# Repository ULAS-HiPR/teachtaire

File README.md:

# Teachtaire

Teachtaire is the telemetry and navigation node in [Ogma](https://sean-osullivan.com/projects/ogma/), the University of Limerick Aeronautics Society's modular avionics stack for high-powered rocketry.

## Role

- Relays stack telemetry over an SX1272 LoRa radio.
- Reads position and timing from a u-blox MAX-M10S GNSS receiver.
- Exchanges telemetry and status over the 500 kbit/s CAN bus.
- Runs on an STM32F072.

## Repository

- `hardware/` - KiCad design and manufacturing outputs.
- `firmware/` - embedded firmware, radio/GNSS probes, and tests.

## Status

Rev 1 firmware and hardware bring-up continue on [`ogma/flight-hardening`](https://github.com/ULAS-HiPR/teachtaire/tree/ogma/flight-hardening). Release-candidate firmware builds and software tests pass, but hardware-in-the-loop validation is still underway. Teachtaire is not yet flight-proven.

## Manufacturing support

Rev 1 PCB fabrication was sponsored through [EasyEDA Education](https://easyeda.com/education) and manufactured by [JLCPCB](https://jlcpcb.com/). The board was designed in KiCad and imported into EasyEDA Pro for the sponsorship and manufacturing workflow.

## More information

See the [Ogma project write-up](https://sean-osullivan.com/projects/ogma/) for the complete stack, bring-up work, and current status.

> [!WARNING]
> This project is archived, and is no longer actively supported.
> Contact us for more details.

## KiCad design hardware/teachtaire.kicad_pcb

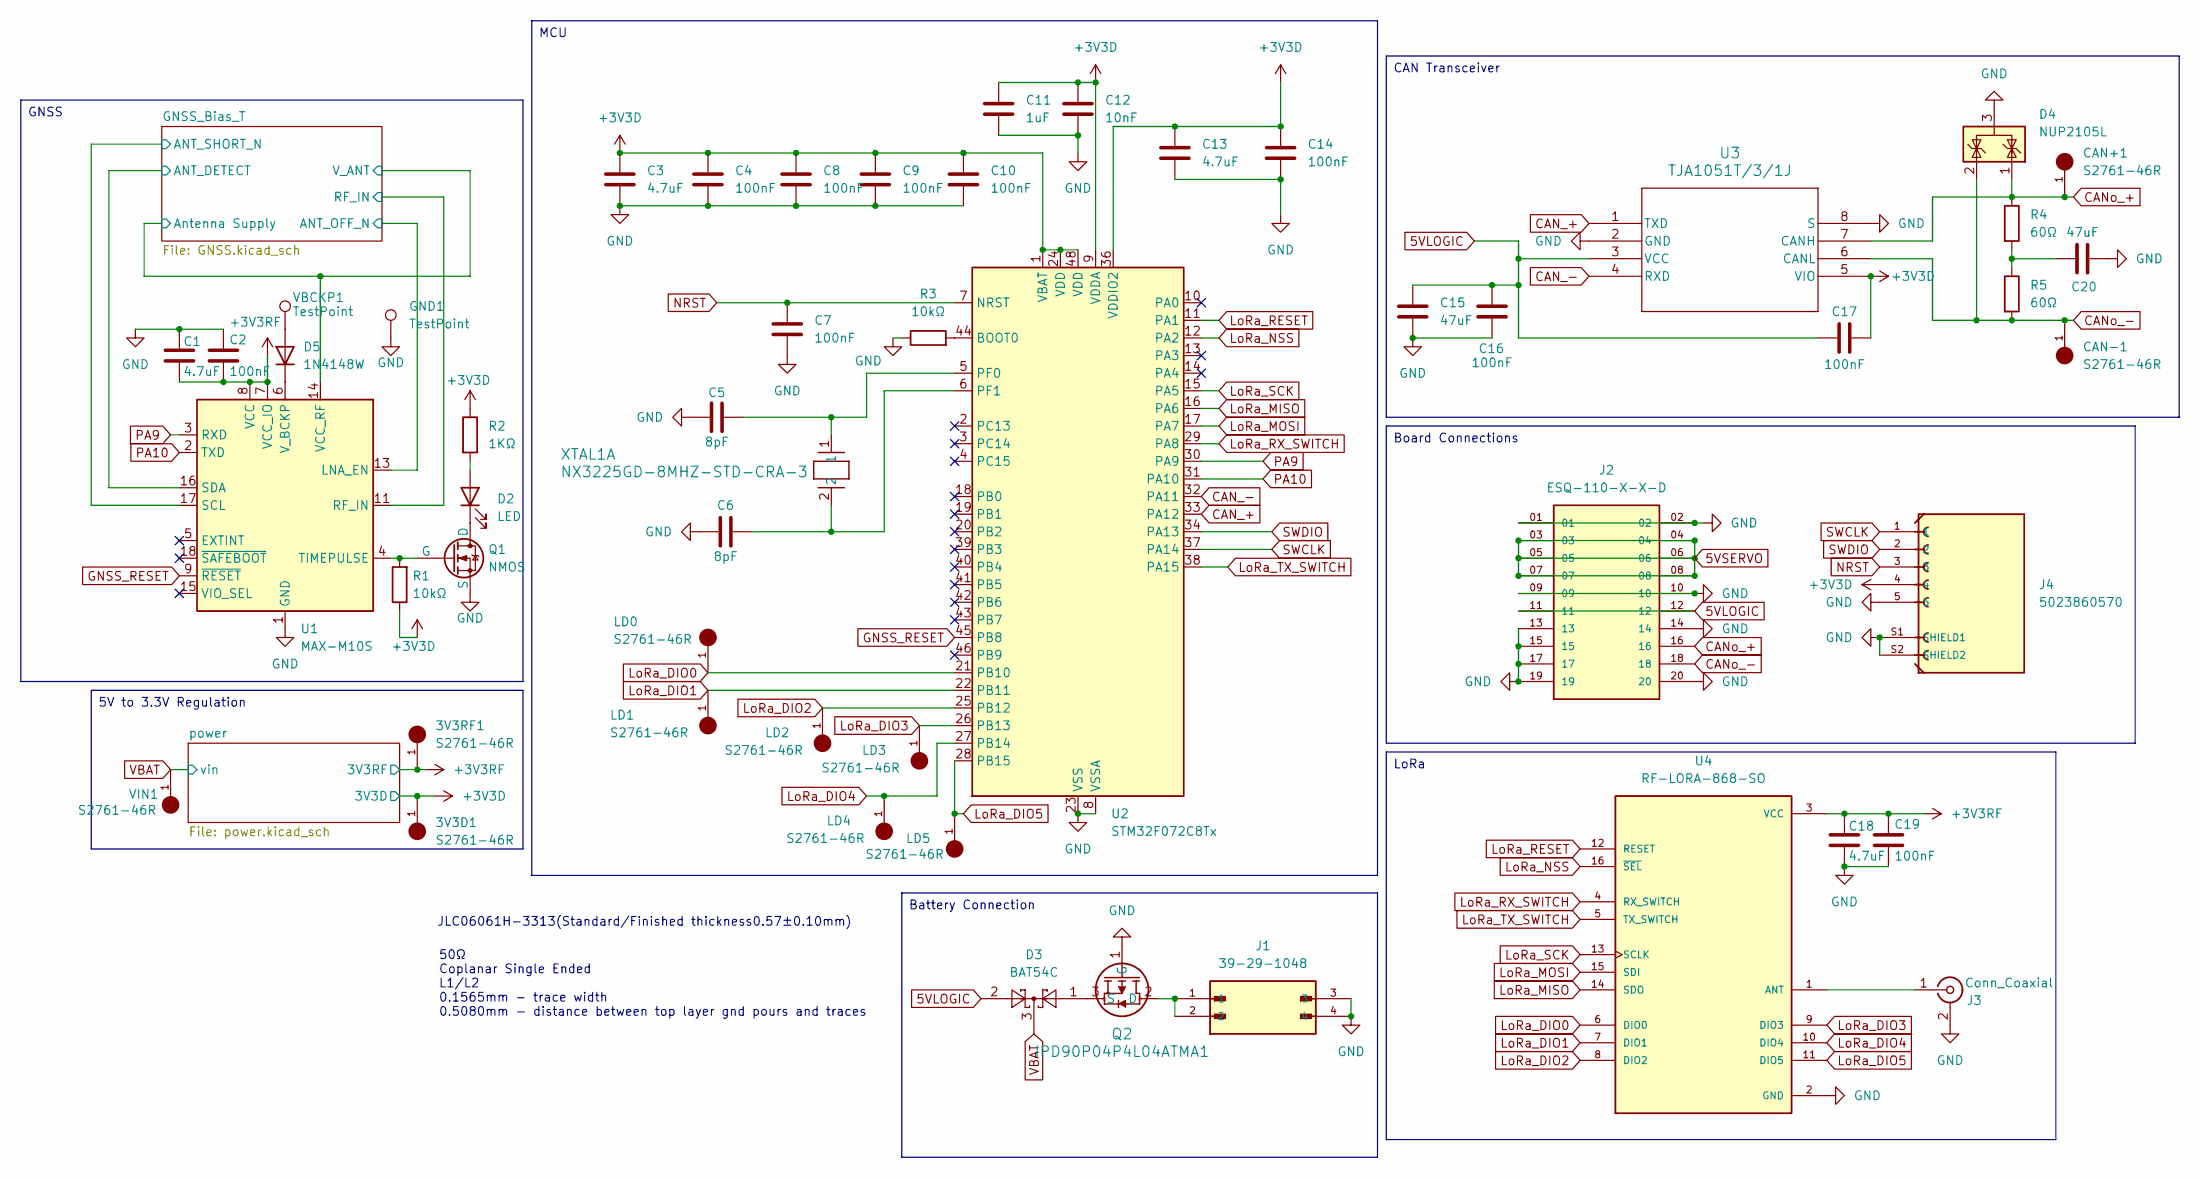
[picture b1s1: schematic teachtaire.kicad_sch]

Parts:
3V3D1, 3V3RF1: S2761-46R; HARWIN_S2761-46R; PARTREV 1
C1, C3, C13, C18: 4.7uF; C_0402_1005Metric
C2, C4, C7, C8, C9, C10, C14, C16, C17, C19: 100nF; C_0402_1005Metric
C5, C6: 8pF; C_0402_1005Metric
C11: 1uF; C_0402_1005Metric
C12: 10nF; C_0603_1608Metric
C15, C20: 47uF; C_0603_1608Metric
CAN+1: S2761-46R; HARWIN_S2761-46R; PARTREV 1
CAN-1: S2761-46R; HARWIN_S2761-46R; PARTREV 1
D2: LED; LED_0402_1005Metric
D3: BAT54C; SOT-23
D4: NUP2105L; SOT-23
D5: 1N4148W; D_SOD-123
GND1: TestPoint; TestPoint_Pad_D2.0mm
J1: 39-29-1048; MOLEX_39-29-1048
J2: ESQ-110-X-X-D; SAMTEC_ESQ-110-14-G-D; PARTREV NA
J3: Conn_Coaxial; SMA_BAT_Wireless_BWSMA-KWE-Z001
J4: 5023860570; MOLEX_5023860570; PARTREV F
LD0, LD1, LD2, LD3, LD4, LD5: S2761-46R; HARWIN_S2761-46R; PARTREV 1
Q1: NMOS; SOT-23
Q2: IPD90P04P4L04ATMA1; PG-TO252-3-313_INF-L
R1, R3: 10kΩ; R_0402_1005Metric
R2: 1KΩ; R_0402_1005Metric
R4, R5: 60Ω; R_0402_1005Metric
U1: MAX-M10S; ublox_MAX
U2: STM32F072C8Tx; LQFP-48_7x7mm_P0.5mm
U3: TJA1051T/3/1J; SO8_SOT96-1_NXP
U4: RF-LORA-868-SO; XCVR_RF-LORA-868-SO
VBCKP1: TestPoint; TestPoint_Pad_D2.0mm
VIN1: S2761-46R; HARWIN_S2761-46R; PARTREV 1
XTAL1: NX3225GD-8MHZ-STD-CRA-3; XTAL_NX3225GD-8MHZ-STD-CRA-3_NDK

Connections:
5VLOGIC: C15.1, C16.1, C17.1, D3.2, J2.11, J2.12, U3.3 (VCC)
5VSERVO: J2.03, J2.04, J2.05, J2.06, J2.07, J2.08
+3V3D: 3V3D1.1, C3.1, C4.1, C8.1, C9.1, C10.1, C11.1, C12.1, C13.1, C14.1, C17.2, J4.4, R1.1, R2.1, U2.1 (VBAT), U2.9 (VDDA), U2.24 (VDD), U2.36 (VDDIO2), U2.48 (VDD), U3.5 (VIO); also elsewhere on the board
+3V3RF: 3V3RF1.1, C1.2, C2.2, C18.1, C19.1, U1.7 (VCC_IO), U1.8 (VCC), U4.3 (VCC); also elsewhere on the board
/GNSS_Bias_T/ANT_DETECT: U1.16 (SDA); also elsewhere on the board
/GNSS_Bias_T/ANT_OFF_N: U1.13 (LNA_EN); also elsewhere on the board
/GNSS_Bias_T/ANT_SHORT_N: U1.17 (SCL); also elsewhere on the board
/GNSS_Bias_T/Antenna Supply: U1.14 (VCC_RF); also elsewhere on the board
/GNSS_Bias_T/RF_IN: U1.11 (RF_IN); also elsewhere on the board
CAN_+: U2.33 (PA12), U3.1 (TXD)
CAN_-: U2.32 (PA11), U3.4 (RXD)
CANo_+: CAN+1.1, D4.1 (K), J2.16, R4.1, U3.7 (CANH); also elsewhere on the board
CANo_-: CAN-1.1, D4.2 (K), J2.18, R5.2, U3.6 (CANL); also elsewhere on the board
GND: C1.1, C2.1, C3.2, C4.2, C5.1, C6.1, C7.2, C8.2, C9.2, C10.2, C11.2, C12.2, C13.2, C14.2, C15.2, C16.2, C18.2, C19.2, C20.2, D4.3 (A), GND1.1, J1.3, J1.4, J2.01, J2.02, J2.09, J2.10, J2.13, J2.14, J2.15, J2.17, J2.19, J2.20, J3.2 (Ext), J4.5, J4.S1 (SHIELD1), J4.S2 (SHIELD2), Q1.3 (S), Q2.1 (G), R3.1, U1.1 (GND), U1.10 (GND), U1.12 (GND), U2.8 (VSSA), U2.23 (VSS), U2.35 (VSS), U2.47 (VSS), U3.2 (GND), U3.8 (S), U4.2 (GND); also elsewhere on the board
GNSS_RESET: U1.9 (~RESET), U2.45 (PB8)
LoRa_DIO0: LD0.1, U2.21 (PB10), U4.6 (DIO0)
LoRa_DIO1: LD1.1, U2.22 (PB11), U4.7 (DIO1)
LoRa_DIO2: LD2.1, U2.25 (PB12), U4.8 (DIO2)
LoRa_DIO3: LD3.1, U2.26 (PB13), U4.9 (DIO3)
LoRa_DIO4: LD4.1, U2.27 (PB14), U4.10 (DIO4)
LoRa_DIO5: LD5.1, U2.28 (PB15), U4.11 (DIO5)
LoRa_MISO: U2.16 (PA6), U4.14 (SDO)
LoRa_MOSI: U2.17 (PA7), U4.15 (SDI)
LoRa_NSS: U2.12 (PA2), U4.16 (~SEL)
LoRa_RESET: U2.11 (PA1), U4.12 (RESET)
LoRa_RX_SWITCH: U2.29 (PA8), U4.4 (RX_SWITCH)
LoRa_SCK: U2.15 (PA5), U4.13 (SCLK)
LoRa_TX_SWITCH: U2.38 (PA15), U4.5 (TX_SWITCH)
NRST: C7.1, J4.3, U2.7 (NRST)
unnamed: C20.1, R4.2, R5.1
unnamed: D2.2 (A), R2.2
unnamed: D2.1 (K), Q1.1 (D)
unnamed 33: D5.2 (A), VBCKP1.1; also elsewhere on the board
unnamed: D5.1 (K), U1.6 (V_BCKP)
unnamed: J3.1 (In), U4.1 (ANT)
unnamed: Q1.2 (G), R1.2, U1.4 (TIMEPULSE)
unnamed: J1.1, J1.2, Q2.2 (D)
unnamed: D3.1, Q2.3 (S)
unnamed: R3.2, U2.44 (BOOT0)
unnamed: C5.2, U2.5 (PF0), XTAL1.1
unnamed: C6.2, U2.6 (PF1), XTAL1.2
PA9: U1.3 (RXD), U2.30 (PA9)
PA10: U1.2 (TXD), U2.31 (PA10)
SWCLK: J4.1, U2.37 (PA14)
SWDIO: J4.2, U2.34 (PA13)
VBAT: D3.3, VIN1.1; also elsewhere on the board

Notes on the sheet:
50Ω Coplanar Single Ended L1/L2 0.1565mm - trace width 0.5080mm - distance between top layer gnd pours and traces
JLC06061H-3313(Standard/Finished thickness0.57±0.10mm)
Board Connections
Battery Connection
LoRa
CAN Transceiver
GNSS
MCU
5V to 3.3V Regulation

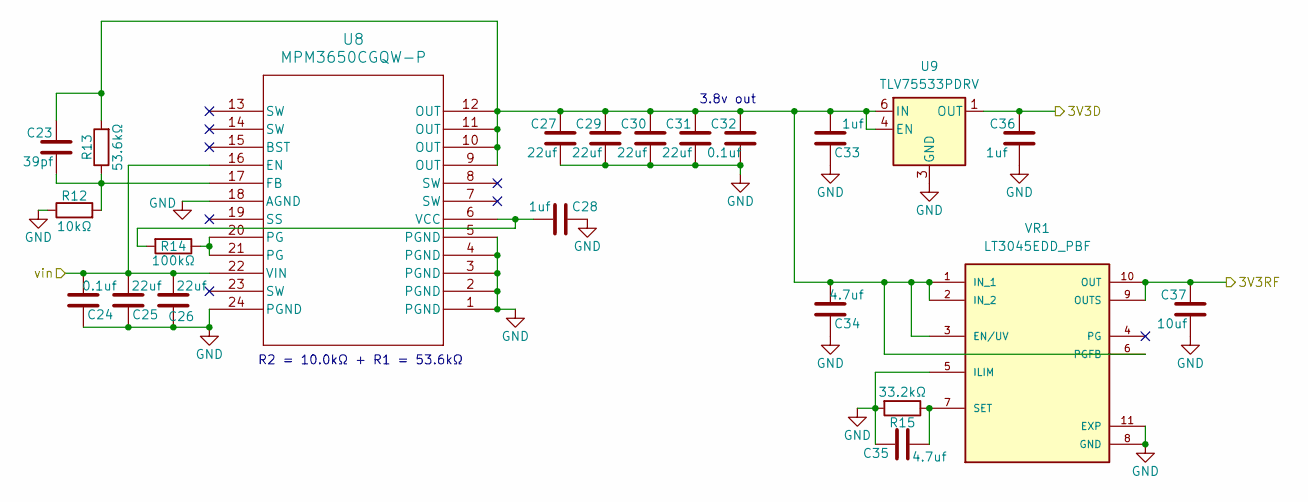
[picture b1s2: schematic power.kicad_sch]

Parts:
C23: 39pf; C_0402_1005Metric
C24, C32: 0.1uf; C_0402_1005Metric
C25, C26, C27, C29, C30, C31: 22uf; C_0603_1608Metric
C28, C33, C36: 1uf; C_0402_1005Metric
C34, C35: 4.7uf; C_0402_1005Metric
C37: 10uf; C_0603_1608Metric
R12: 10kΩ; R_0402_1005Metric
R13: 53.6kΩ; R_0402_1005Metric
R14: 100kΩ; R_0402_1005Metric
R15: 33.2kΩ; R_0402_1005Metric
U8: MPM3650CGQW-P; QFN-24_MPM3650_MNP
U9: TLV75533PDRV; WSON-6-1EP_2x2mm_P0.65mm_EP1x1.6mm
VR1: LT3045EDD_PBF; SON50P300X300X80-11N; PARTREV C

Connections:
+3V3D: C36.1, U9.1 (OUT); also elsewhere on the board
+3V3RF: C37.1, VR1.9 (OUTS), VR1.10 (OUT); also elsewhere on the board
GND: C24.1, C25.1, C26.1, C27.2, C28.1, C29.2, C30.2, C31.2, C32.2, C33.1, C34.1, C35.1, C36.2, C37.2, R12.1, R15.2, U8.1 (PGND), U8.2 (PGND), U8.3 (PGND), U8.4 (PGND), U8.5 (PGND), U8.18 (AGND), U8.24 (PGND), U9.3 (GND), U9.7 (GND), VR1.5 (ILIM), VR1.8 (GND), VR1.11 (EXP); also elsewhere on the board
unnamed: R14.1, U8.20 (PG), U8.21 (PG)
unnamed: C23.2, R12.2, R13.1, U8.17 (FB)
unnamed: C28.2, R14.2, U8.6 (VCC)
unnamed: C23.1, C27.1, C29.1, C30.1, C31.1, C32.1, C33.2, C34.2, R13.2, U8.9 (OUT), U8.10 (OUT), U8.11 (OUT), U8.12 (OUT), U9.4 (EN), U9.6 (IN), VR1.1 (IN_1), VR1.2 (IN_2), VR1.3 (EN/UV), VR1.6 (PGFB)
unnamed: C35.2, R15.1, VR1.7 (SET)
VBAT: C24.2, C25.2, C26.2, U8.16 (EN), U8.22 (VIN); also elsewhere on the board

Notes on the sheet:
3.8v out
R2 = 10.0kΩ + R1 = 53.6kΩ

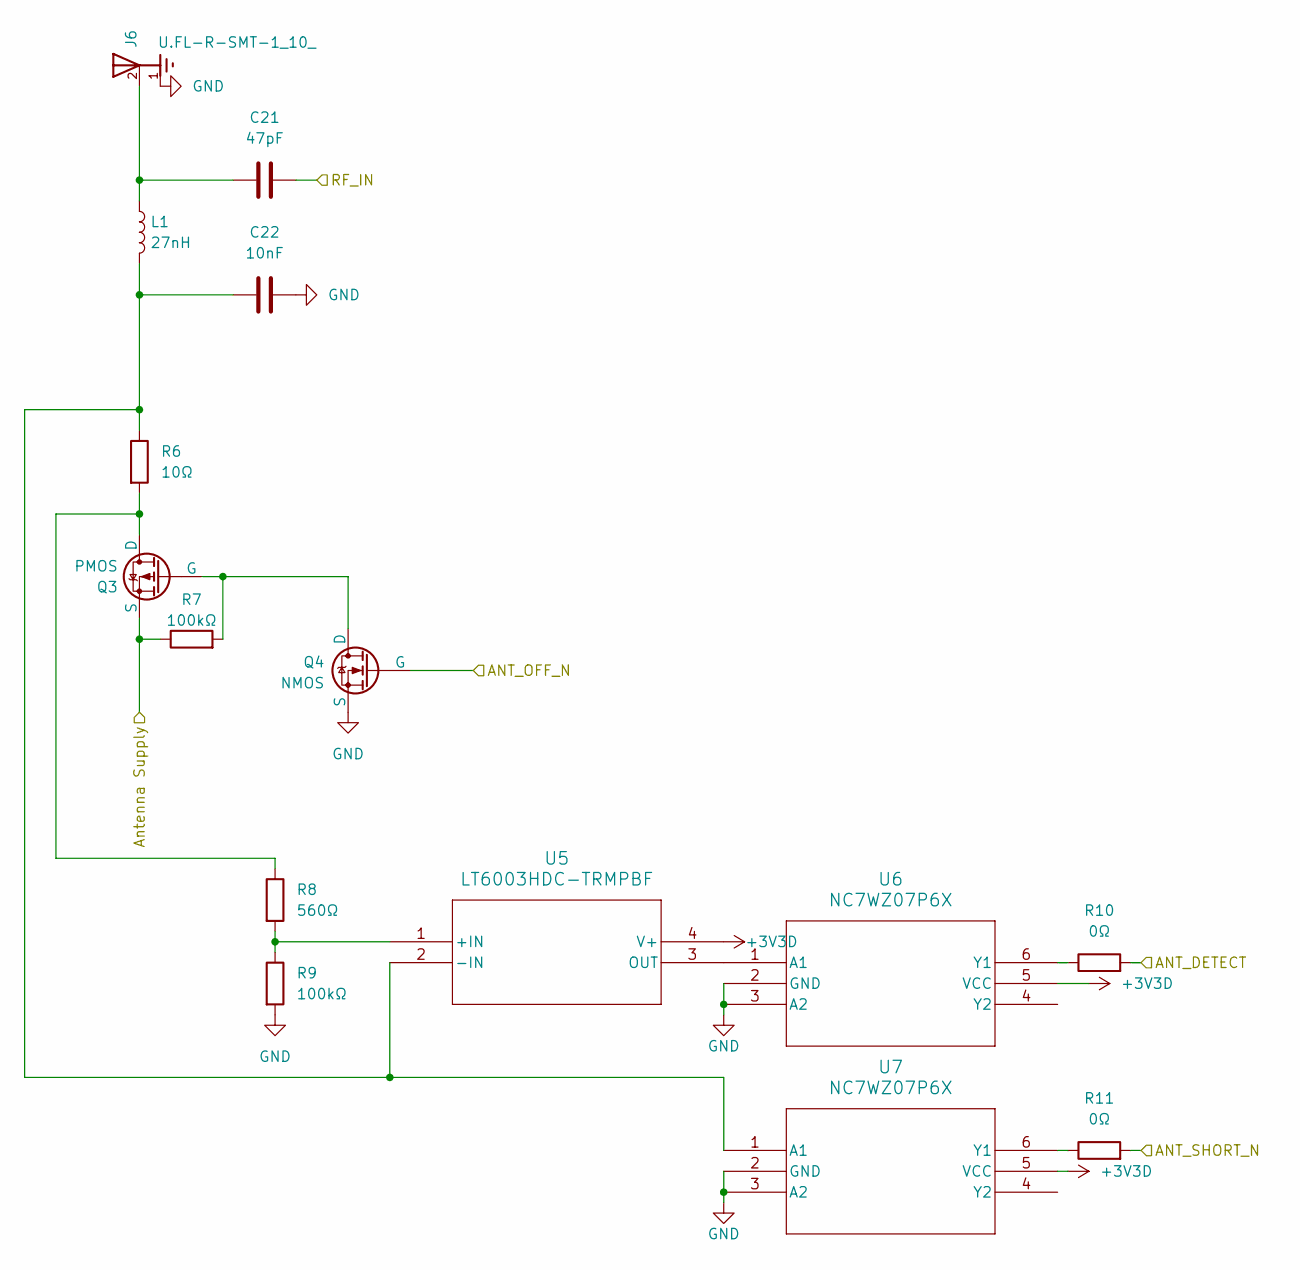
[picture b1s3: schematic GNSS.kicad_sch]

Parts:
C21: 47pF; C_0402_1005Metric
C22: 10nF; C_0603_1608Metric
J6: U.FL-R-SMT-1_10_; HRS_U.FL-R-SMT-1_10_
L1: 27nH; L_0402_1005Metric
Q3: PMOS; SOT-23
Q4: NMOS; SOT-23
R6: 10Ω; R_0402_1005Metric
R7, R9: 100kΩ; R_0402_1005Metric
R8: 560Ω; R_0402_1005Metric
R10, R11: 0Ω; R_0402_1005Metric
U5: LT6003HDC-TRMPBF; DC_4_ADI
U6, U7: NC7WZ07P6X; SC-88&slash_SC70-6&slash_SOT-363_419B-02_ONS

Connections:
+3V3D: U5.4 (V+), U6.5 (VCC), U7.5 (VCC); also elsewhere on the board
/GNSS_Bias_T/ANT_DETECT: R10.2; also elsewhere on the board
/GNSS_Bias_T/ANT_OFF_N: Q4.2 (G); also elsewhere on the board
/GNSS_Bias_T/ANT_SHORT_N: R11.2; also elsewhere on the board
/GNSS_Bias_T/Antenna Supply: Q3.3 (S), R7.1; also elsewhere on the board
/GNSS_Bias_T/RF_IN: C21.2; also elsewhere on the board
GND: C22.2, J6.1, J6.3, Q4.3 (S), R9.2, U6.2 (GND), U6.3 (A2), U7.2 (GND), U7.3 (A2); also elsewhere on the board
unnamed: C21.1, J6.2, L1.1
unnamed: Q3.1 (D), R6.2, R8.1
unnamed: Q3.2 (G), Q4.1 (D), R7.2
unnamed: R8.2, R9.1, U5.1 (+IN)
unnamed: C22.1, L1.2, R6.1, U5.2 (-IN), U7.1 (A1)
unnamed: U5.3 (OUT), U6.1 (A1)
unnamed: R10.1, U6.6 (Y1)
unnamed: R11.1, U7.6 (Y1)

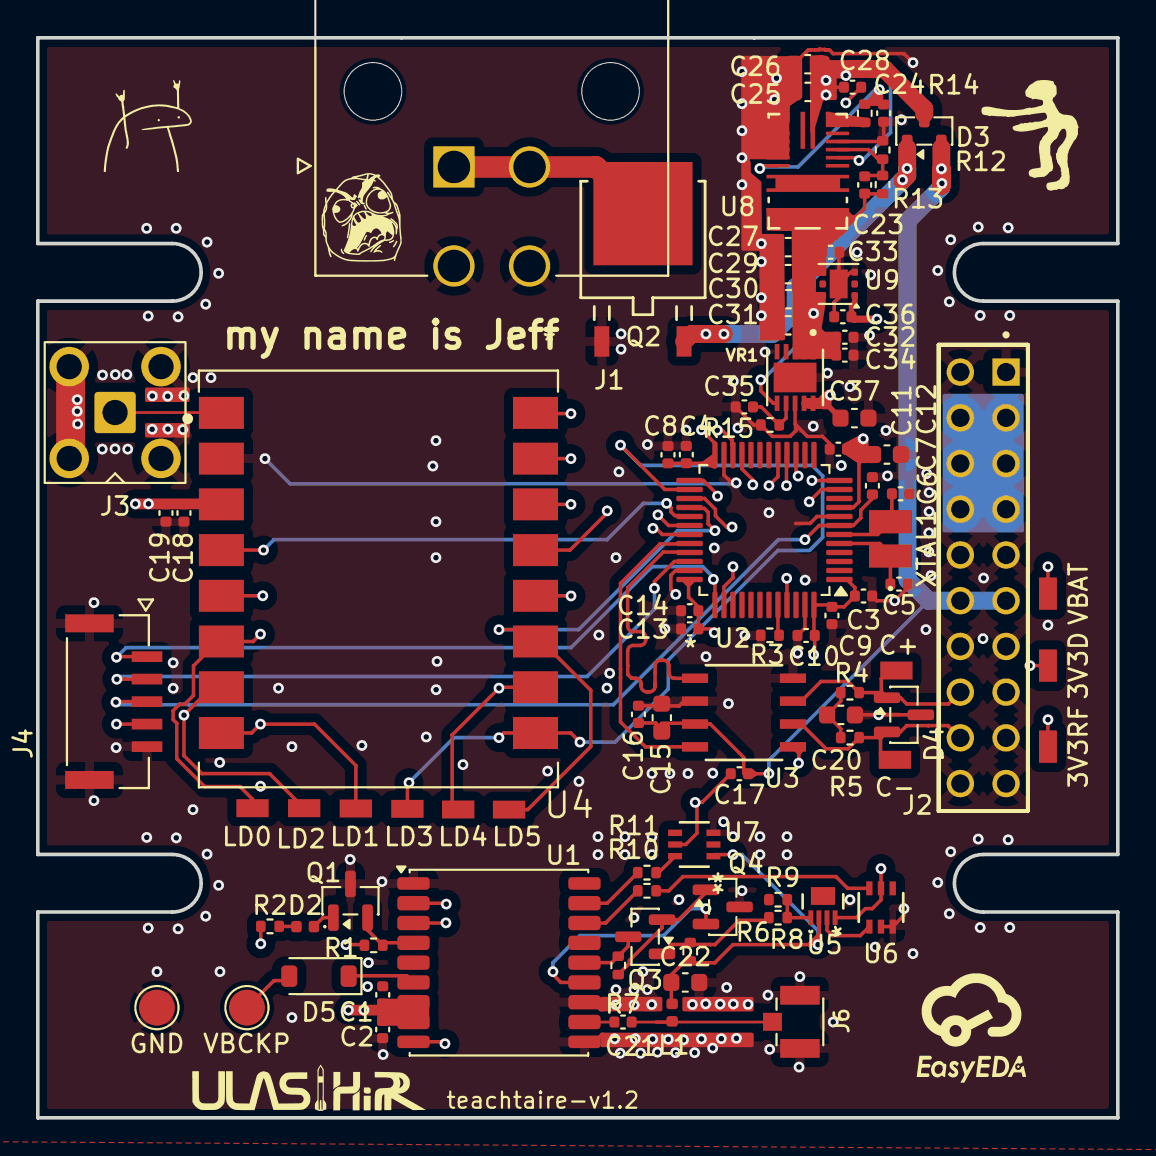
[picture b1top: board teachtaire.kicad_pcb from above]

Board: 6 copper layers, 60.0 x 60.0 mm, 90 parts (0 on the bottom side), 59 nets.

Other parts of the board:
3V3D, 3V3RF: S2761-46R; HARWIN_S2761-46R
C+: S2761-46R; HARWIN_S2761-46R
C-: S2761-46R; HARWIN_S2761-46R
GND: TestPoint; TestPoint_Pad_D2.0mm
VBAT: S2761-46R; HARWIN_S2761-46R
VBCKP: TestPoint; TestPoint_Pad_D2.0mm

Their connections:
+3V3D: 3V3D.1; also elsewhere on the board
+3V3RF: 3V3RF.1; also elsewhere on the board
CANo_+: C+.1; also elsewhere on the board
CANo_-: C-.1; also elsewhere on the board
GND: GND.1; also elsewhere on the board
unnamed 33: VBCKP.1; also elsewhere on the board
VBAT: VBAT.1; also elsewhere on the board

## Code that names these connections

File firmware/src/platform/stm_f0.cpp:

#if F0
#include "stm_f0.h"


CAN_HandleTypeDef hcan;
SPI_HandleTypeDef hspi1;
UART_HandleTypeDef huart1;

void HAL_MspInit(void)
{

  /* USER CODE BEGIN MspInit 0 */

  /* USER CODE END MspInit 0 */

  __HAL_RCC_SYSCFG_CLK_ENABLE();
  __HAL_RCC_PWR_CLK_ENABLE();

  /* System interrupt init*/
  /* PendSV_IRQn interrupt configuration */
  HAL_NVIC_SetPriority(PendSV_IRQn, 3, 0);

  /* USER CODE BEGIN MspInit 1 */

  /* USER CODE END MspInit 1 */
}



/**
  * @brief CAN Initialization Function
  * @param None
  * @retval None
  */
void MX_CAN_Init(void)
{

  /* USER CODE BEGIN CAN_Init 0 */

  /* USER CODE END CAN_Init 0 */

  /* USER CODE BEGIN CAN_Init 1 */

  /* USER CODE END CAN_Init 1 */
  hcan.Instance = CAN;
  hcan.Init.Prescaler = 6;
  //hcan.Init.Mode = CAN_MODE_LOOPBACK;
  hcan.Init.Mode = CAN_MODE_NORMAL;
  hcan.Init.SyncJumpWidth = CAN_SJW_1TQ;
  hcan.Init.TimeSeg1 = CAN_BS1_13TQ;
  hcan.Init.TimeSeg2 = CAN_BS2_2TQ;
  hcan.Init.TimeTriggeredMode = DISABLE;
  hcan.Init.AutoBusOff = DISABLE;
  hcan.Init.AutoWakeUp = DISABLE;
  hcan.Init.AutoRetransmission = ENABLE;
  hcan.Init.ReceiveFifoLocked = DISABLE;
  hcan.Init.TransmitFifoPriority = DISABLE;
  if (HAL_CAN_Init(&hcan) != HAL_OK)
  {
    Error_Handler();
  }
  /* USER CODE BEGIN CAN_Init 2 */

  /* USER CODE END CAN_Init 2 */

}


/**
  * @brief CAN MSP Initialization
  * This function configures the hardware resources used in this example
  * @param hcan: CAN handle pointer
  * @retval None
  */
void HAL_CAN_MspInit(CAN_HandleTypeDef* hcan)
{
  GPIO_InitTypeDef GPIO_InitStruct = {0};
  if(hcan->Instance==CAN)
  {
    /* USER CODE BEGIN CAN_MspInit 0 */

    /* USER CODE END CAN_MspInit 0 */
    /* Peripheral clock enable */
    __HAL_RCC_CAN1_CLK_ENABLE();

    __HAL_RCC_GPIOA_CLK_ENABLE();
    /**CAN GPIO Configuration
    PA11     ------> CAN_RX
    PA12     ------> CAN_TX
    */
    GPIO_InitStruct.Pin = GPIO_PIN_11|GPIO_PIN_12;
    GPIO_InitStruct.Mode = GPIO_MODE_AF_PP;
    GPIO_InitStruct.Pull = GPIO_NOPULL;
    GPIO_InitStruct.Speed = GPIO_SPEED_FREQ_HIGH;
    GPIO_InitStruct.Alternate = GPIO_AF4_CAN;
    HAL_GPIO_Init(GPIOA, &GPIO_InitStruct);

    /* USER CODE BEGIN CAN_MspInit 1 */

    /* USER CODE END CAN_MspInit 1 */

  }

}

/**
  * @brief CAN MSP De-Initialization
  * This function freeze the hardware resources used in this example
  * @param hcan: CAN handle pointer
  * @retval None
  */
void HAL_CAN_MspDeInit(CAN_HandleTypeDef* hcan)
{
  if(hcan->Instance==CAN)
  {
    /* USER CODE BEGIN CAN_MspDeInit 0 */

    /* USER CODE END CAN_MspDeInit 0 */
    /* Peripheral clock disable */
    __HAL_RCC_CAN1_CLK_DISABLE();

    /**CAN GPIO Configuration
    PA11     ------> CAN_RX
    PA12     ------> CAN_TX
    */
    HAL_GPIO_DeInit(GPIOA, GPIO_PIN_11|GPIO_PIN_12);

    /* USER CODE BEGIN CAN_MspDeInit 1 */

    /* USER CODE END CAN_MspDeInit 1 */
  }

}

void MX_USART1_UART_Init(void)
{

  /* USER CODE BEGIN USART1_Init 0 */

  /* USER CODE END USART1_Init 0 */

  /* USER CODE BEGIN USART1_Init 1 */

  /* USER CODE END USART1_Init 1 */
  huart1.Instance = USART1;
  huart1.Init.BaudRate = 9600U;
  huart1.Init.WordLength = UART_WORDLENGTH_8B;
  huart1.Init.StopBits = UART_STOPBITS_1;
  huart1.Init.Parity = UART_PARITY_NONE;
  huart1.Init.Mode = UART_MODE_TX_RX;
  huart1.Init.HwFlowCtl = UART_HWCONTROL_NONE;
  huart1.Init.OverSampling = UART_OVERSAMPLING_16;
  huart1.AdvancedInit.AdvFeatureInit = UART_ADVFEATURE_NO_INIT;
  if (HAL_UART_Init(&huart1) != HAL_OK)
  {
    Error_Handler();
  }
  /* USER CODE BEGIN USART1_Init 2 */

  /* USER CODE END USART1_Init 2 */

}

/**
  * @brief UART MSP Initialization
  * This function configures the hardware resources used in this example
  * @param huart: UART handle pointer
  * @retval None
  */
void HAL_UART_MspInit(UART_HandleTypeDef* huart)
{
  GPIO_InitTypeDef GPIO_InitStruct = {0};
  if(huart->Instance==USART1)
  {
    /* USER CODE BEGIN USART1_MspInit 0 */

    /* USER CODE END USART1_MspInit 0 */
    /* Peripheral clock enable */
    __HAL_RCC_USART1_CLK_ENABLE();

    __HAL_RCC_GPIOA_CLK_ENABLE();
    /**USART1 GPIO Configuration
    PA9     ------> USART1_TX
    PA10     ------> USART1_RX
    */
    GPIO_InitStruct.Pin = GNSS_UART_TX_PIN|GNSS_UART_RX_PIN;
    GPIO_InitStruct.Mode = GPIO_MODE_AF_PP;
    GPIO_InitStruct.Pull = GPIO_PULLUP;
    GPIO_InitStruct.Speed = GPIO_SPEED_FREQ_HIGH;
    GPIO_InitStruct.Alternate = GPIO_AF1_USART1;
    HAL_GPIO_Init(GPIOA, &GPIO_InitStruct);

    /* USER CODE BEGIN USART1_MspInit 1 */

    /* USER CODE END USART1_MspInit 1 */

  }

}

/**
  * @brief UART MSP De-Initialization
  * This function freeze the hardware resources used in this example
  * @param huart: UART handle pointer
  * @retval None
  */
void HAL_UART_MspDeInit(UART_HandleTypeDef* huart)
{
  if(huart->Instance==USART1)
  {
    /* USER CODE BEGIN USART1_MspDeInit 0 */

    /* USER CODE END USART1_MspDeInit 0 */
    /* Peripheral clock disable */
    __HAL_RCC_USART1_CLK_DISABLE();

    /**USART1 GPIO Configuration
    PA9     ------> USART1_TX
    PA10     ------> USART1_RX
    */
    HAL_GPIO_DeInit(GPIOA, GNSS_UART_TX_PIN|GNSS_UART_RX_PIN);

    /* USER CODE BEGIN USART1_MspDeInit 1 */

    /* USER CODE END USART1_MspDeInit 1 */
  }

}

void MX_SPI1_Init(void)
{

  /* USER CODE BEGIN SPI1_Init 0 */

  /* USER CODE END SPI1_Init 0 */

  /* USER CODE BEGIN SPI1_Init 1 */

  /* USER CODE END SPI1_Init 1 */
  /* SPI1 parameter configuration*/
  hspi1.Instance = SPI1;
  hspi1.Init.Mode = SPI_MODE_MASTER;
  hspi1.Init.Direction = SPI_DIRECTION_2LINES;
  hspi1.Init.DataSize = SPI_DATASIZE_8BIT;
  hspi1.Init.CLKPolarity = SPI_POLARITY_LOW;
  hspi1.Init.CLKPhase = SPI_PHASE_1EDGE;
  hspi1.Init.NSS = SPI_NSS_SOFT;
  hspi1.Init.BaudRatePrescaler = SPI_BAUDRATEPRESCALER_8;
  hspi1.Init.FirstBit = SPI_FIRSTBIT_MSB;
  hspi1.Init.TIMode = SPI_TIMODE_DISABLE;
  hspi1.Init.CRCCalculation = SPI_CRCCALCULATION_DISABLE;

  if (HAL_SPI_Init(&hspi1) != HAL_OK)
  {
    Error_Handler();
  }
  /* USER CODE BEGIN SPI1_Init 2 */

  /* USER CODE END SPI1_Init 2 */

}


void HAL_SPI_MspInit(SPI_HandleTypeDef* hspi)
{
    if (hspi->Instance != SPI1) {
        return;
    }

    SPI_GPIO_CLK_ENABLE();
    __HAL_RCC_SPI1_CLK_ENABLE();

    GPIO_InitTypeDef GPIO_InitStruct = {0};
    GPIO_InitStruct.Pin = SPI_SCK_PIN | SPI_MISO_PIN | SPI_MOSI_PIN;
    GPIO_InitStruct.Mode = GPIO_MODE_AF_PP;
    GPIO_InitStruct.Pull = GPIO_NOPULL;
    GPIO_InitStruct.Speed = GPIO_SPEED_FREQ_HIGH;
    GPIO_InitStruct.Alternate = GPIO_AF0_SPI1;
    HAL_GPIO_Init(SPI_GPIO_PORT, &GPIO_InitStruct);

    GPIO_InitStruct.Pin = RADIO_CS_PIN ;
    GPIO_InitStruct.Mode = GPIO_MODE_OUTPUT_PP;
    GPIO_InitStruct.Pull = GPIO_NOPULL;
    GPIO_InitStruct.Speed = GPIO_SPEED_FREQ_HIGH;
    HAL_GPIO_Init(GPIOA, &GPIO_InitStruct);
    HAL_GPIO_WritePin(RADIO_CS_PORT, RADIO_CS_PIN, GPIO_PIN_SET);

}

/**
  * @brief SPI MSP De-Initialization
  * This function freeze the hardware resources used in this example
  * @param hspi: SPI handle pointer
  * @retval None
  */
void HAL_SPI_MspDeInit(SPI_HandleTypeDef* hspi)
{
  if(hspi->Instance==SPI1)
  {
    /* USER CODE BEGIN SPI1_MspDeInit 0 */

    /* USER CODE END SPI1_MspDeInit 0 */
    /* Peripheral clock disable */
    __HAL_RCC_SPI1_CLK_DISABLE();

    /**SPI1 GPIO Configuration
    PA5     ------> SPI1_SCK
    PA6     ------> SPI1_MISO
    PA7     ------> SPI1_MOSI
    */
    HAL_GPIO_DeInit(GPIOA, SPI_SCK_PIN|SPI_MISO_PIN|SPI_MOSI_PIN | RADIO_CS_PIN);

    /* USER CODE BEGIN SPI1_MspDeInit 1 */

    /* USER CODE END SPI1_MspDeInit 1 */
  }

}

void MX_GPIO_Init(void)
{
  GPIO_InitTypeDef GPIO_InitStruct = {0};
  /* USER CODE BEGIN MX_GPIO_Init_1 */

  /* USER CODE END MX_GPIO_Init_1 */

  /* GPIO Ports Clock Enable */
  __HAL_RCC_GPIOA_CLK_ENABLE();
  __HAL_RCC_GPIOB_CLK_ENABLE();

  /*Configure GPIO pin Output Level */
  HAL_GPIO_WritePin(GPIOA, RADIO_RESET_PIN|RADIO_RX_SW_PIN|RADIO_TX_SW_PIN, GPIO_PIN_RESET);

  /*Configure GPIO pin Output Level */
  HAL_GPIO_WritePin(GPIOB, GNSS_RESET_PIN, GPIO_PIN_RESET);

  /*Configure GPIO pins : LoRa_Reset_Pin LoRa_NSS_Pin LoRa_RX_Switch_Pin */
  GPIO_InitStruct.Pin = RADIO_RESET_PIN|RADIO_RX_SW_PIN|RADIO_TX_SW_PIN;
  GPIO_InitStruct.Mode = GPIO_MODE_OUTPUT_PP;
  GPIO_InitStruct.Pull = GPIO_NOPULL;
  GPIO_InitStruct.Speed = GPIO_SPEED_FREQ_LOW;
  HAL_GPIO_Init(GPIOA, &GPIO_InitStruct);

  /*Configure GPIO pins : LoRa_TX_Switch_Pin GNSS_RESET_Pin */
  GPIO_InitStruct.Pin = GNSS_RESET_PIN;
  GPIO_InitStruct.Mode = GPIO_MODE_OUTPUT_PP;
  GPIO_InitStruct.Pull = GPIO_NOPULL;
  GPIO_InitStruct.Speed = GPIO_SPEED_FREQ_LOW;
  HAL_GPIO_Init(GPIOB, &GPIO_InitStruct);

  /* USER CODE BEGIN MX_GPIO_Init_2 */

  /* USER CODE END MX_GPIO_Init_2 */
}
#endif // F0

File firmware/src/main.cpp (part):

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
constexpr uint32_t REPORT_MAGIC = 0x54434854U; // 'TCHT'

constexpr uint16_t LORA_RESET_PIN = GPIO_PIN_1;
constexpr uint16_t LORA_NSS_PIN = GPIO_PIN_2;
constexpr uint16_t LORA_SCK_PIN = GPIO_PIN_5;
constexpr uint16_t LORA_MISO_PIN = GPIO_PIN_6;
constexpr uint16_t LORA_MOSI_PIN = GPIO_PIN_7;
constexpr uint16_t LORA_RX_SWITCH_PIN = GPIO_PIN_8;
constexpr uint16_t LORA_TX_SWITCH_PIN = GPIO_PIN_15;

constexpr uint16_t GNSS_RESET_PIN = GPIO_PIN_8;
constexpr uint16_t GNSS_TX_PIN = GPIO_PIN_9;
constexpr uint16_t GNSS_RX_PIN = GPIO_PIN_10;
constexpr uint32_t CAN_HEARTBEAT_PERIOD_MS = 1000U;
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    __HAL_RCC_GPIOA_CLK_ENABLE();
    __HAL_RCC_GPIOB_CLK_ENABLE();

    gpio_output(GPIOA, LORA_NSS_PIN, GPIO_PIN_SET);
    gpio_output(GPIOA, LORA_RESET_PIN, GPIO_PIN_RESET);
    gpio_output(GPIOA, LORA_RX_SWITCH_PIN, GPIO_PIN_RESET);
    gpio_output(GPIOA, LORA_TX_SWITCH_PIN, GPIO_PIN_RESET);
    gpio_output(GPIOB, GNSS_RESET_PIN, GPIO_PIN_SET);

    gpio_af(GPIOA, LORA_SCK_PIN | LORA_MISO_PIN | LORA_MOSI_PIN, GPIO_AF0_SPI1, GPIO_NOPULL);
    gpio_af(GPIOA, GNSS_TX_PIN | GNSS_RX_PIN, GPIO_AF1_USART1, GPIO_PULLUP);

    report.gpio_ok = 1U;
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
void lora_reset_write(bool high, void*)
{
    HAL_GPIO_WritePin(GPIOA, LORA_RESET_PIN, high ? GPIO_PIN_SET : GPIO_PIN_RESET);
}

void lora_delay_ms(uint32_t ms, void*)
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{
    HAL_GPIO_WritePin(
        GPIOA,
        LORA_RX_SWITCH_PIN,
        mode == sx1272_switch_mode_t::RX ? GPIO_PIN_SET : GPIO_PIN_RESET
    );

    HAL_GPIO_WritePin(
        GPIOA,
        LORA_TX_SWITCH_PIN,
        mode == sx1272_switch_mode_t::TX ? GPIO_PIN_SET : GPIO_PIN_RESET
    );
}

void gnss_reset()
{
    HAL_GPIO_WritePin(GPIOB, GNSS_RESET_PIN, GPIO_PIN_RESET);
    HAL_Delay(20U);
    HAL_GPIO_WritePin(GPIOB, GNSS_RESET_PIN, GPIO_PIN_SET);
    HAL_Delay(100U);
}

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    }
    gnss_reset();

    SPI_STM spi(&hspi1, GPIOA, LORA_NSS_PIN);
    UART_STM uart(&huart1);

    sx1272_pins_t lora_pins{};
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
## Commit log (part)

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2026-01-13 code inital commit
2026-01-20 Circuit laid out
    I forgot github existed sorry, need to assign footprints and decide on pins to use on the MCU, then route the PCB
2026-01-24 Added values to components
2026-01-29 Finished Schematic and Routed PCB
2026-01-30 minorest of changes
2026-01-30 ready to roll
2026-02-03 3d model made
2026-02-10 Changes from Reddit review 1
    Changed connector, impedance matched the RF traces, changed board to square
2026-02-11 lots to be sorted
2026-02-22 many fatal fuck-ups found
2026-02-22 fixed the fuck-ups
2026-02-23 power and main routing done, just need to set rf trace width
2026-02-23 good to go
2026-02-23 ddio pins
2026-02-23 ready for review the twost
2026-02-26 crimes
2026-02-27 ready to go, nearly
2026-03-01 ready 2 order
2026-03-05 Adding inital files
2026-03-05 removing ds store
2026-03-05 adding PIO file
2026-03-31 hardware done
2026-05-18 feat(sil): update comheadan + linux platform config
2026-06-05 Add Teachtaire GNSS and LoRa bring-up
2026-06-17 Add GNSS status diagnostics
2026-06-18 Add Teachtaire STM32F072 board config
2026-06-24 feat: basic setup complete
2026-06-24 main loop reads lora successful and all runs ok
2026-06-25 Add Teachtaire LoRa link test firmware
2026-06-26 some stuff works maybe
2026-06-26 radio working, gps hopefully outside
2026-06-26 locking down teachtaire
2026-06-27 can debugging
2026-06-29 minor debugging changes
2026-06-29 updating submodules
2026-06-29 sync bit
2026-06-30 Send GNSS packets over LoRa
